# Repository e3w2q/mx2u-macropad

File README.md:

# MX2U!

Happy Holidays Macro Pad.

## What is the MX2U! ?

MX2U! is a macro pad for MX switches that can be used for fun at certain times of the year.

You can place a single 2U key or two 1U keys on this macro pad.

Note: When using the 2U key, the backlight goes directly into your eyes!

## Link

[Hardware data (PCB)](pcb/)

[Firmware](https://github.com/e3w2q/qmk_firmware/tree/e3w2q/keyboards/e3w2q/mx2u)

[PCBの入手方法](doc/pcb_order_guide_jp.md)

[パーツリスト](doc/bom_list_jp.md)

[ビルドガイド](doc/readme_jp.md)

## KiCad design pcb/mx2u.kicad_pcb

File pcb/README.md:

# MX2U! PCB Data

## Schematic
[Schematic PDF](../doc/ukiha.pdf?raw=true)

## PCB Layout

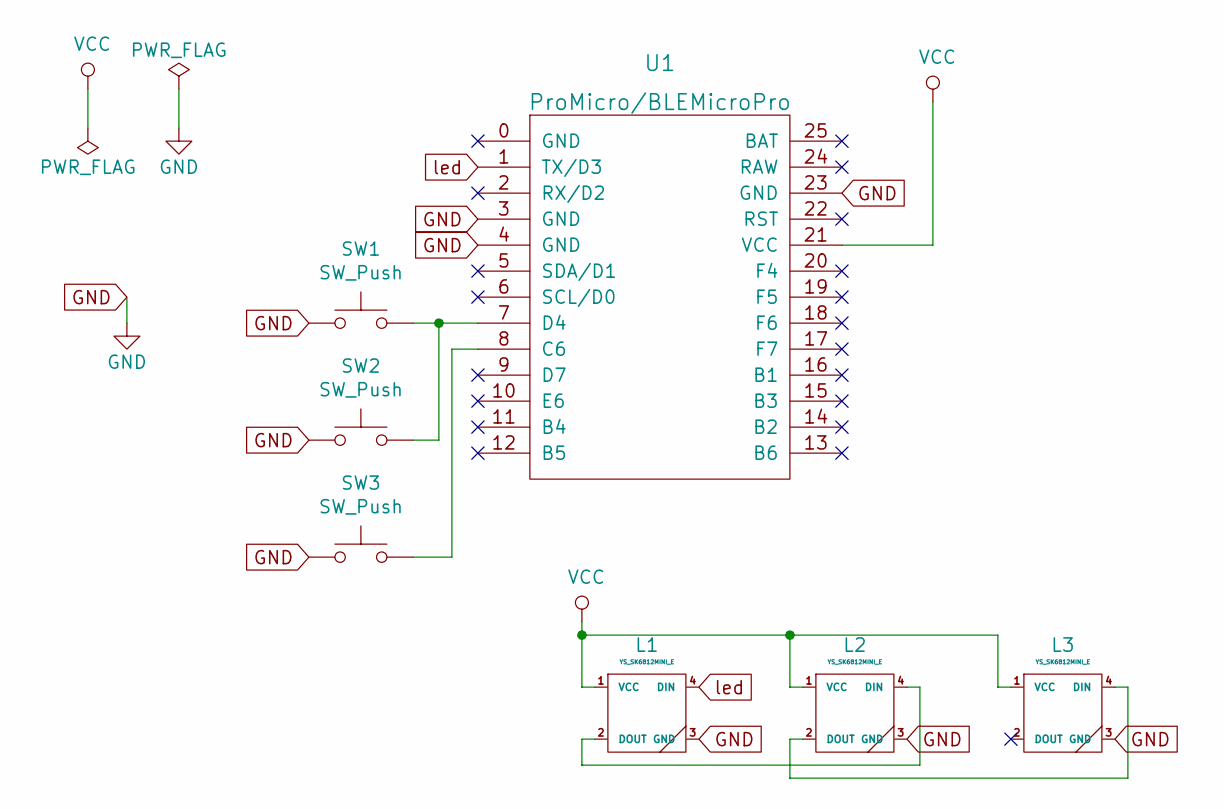
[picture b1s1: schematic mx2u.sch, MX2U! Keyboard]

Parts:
L1, L2: YS_SK6812MINI_E; YS-SK6812MINI-E
L3: YS_SK6812MINI_E; NeoPixcel_Diffused_5mm_Through_Hole_LED
SW1, SW2, SW3: SW_Push; CherryMX_MidHeight
U1: ProMicro/BLEMicroPro; ArduinoProMicro_ConThrough

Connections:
GND: L1.3 (GND), L2.3 (GND), L3.3 (GND), SW1.1, SW2.1, SW3.1, U1.3 (GND), U1.4 (GND), U1.23 (GND)
unnamed: L1.2 (DOUT), L2.4 (DIN)
unnamed: L2.2 (DOUT), L3.4 (DIN)
unnamed: SW1.2, SW2.2, U1.7 (D4)
unnamed: SW3.2, U1.8 (C6)
VCC: L1.1 (VCC), L2.1 (VCC), L3.1 (VCC), U1.21 (VCC)
led: L1.4 (DIN), U1.1 (TX/D3)

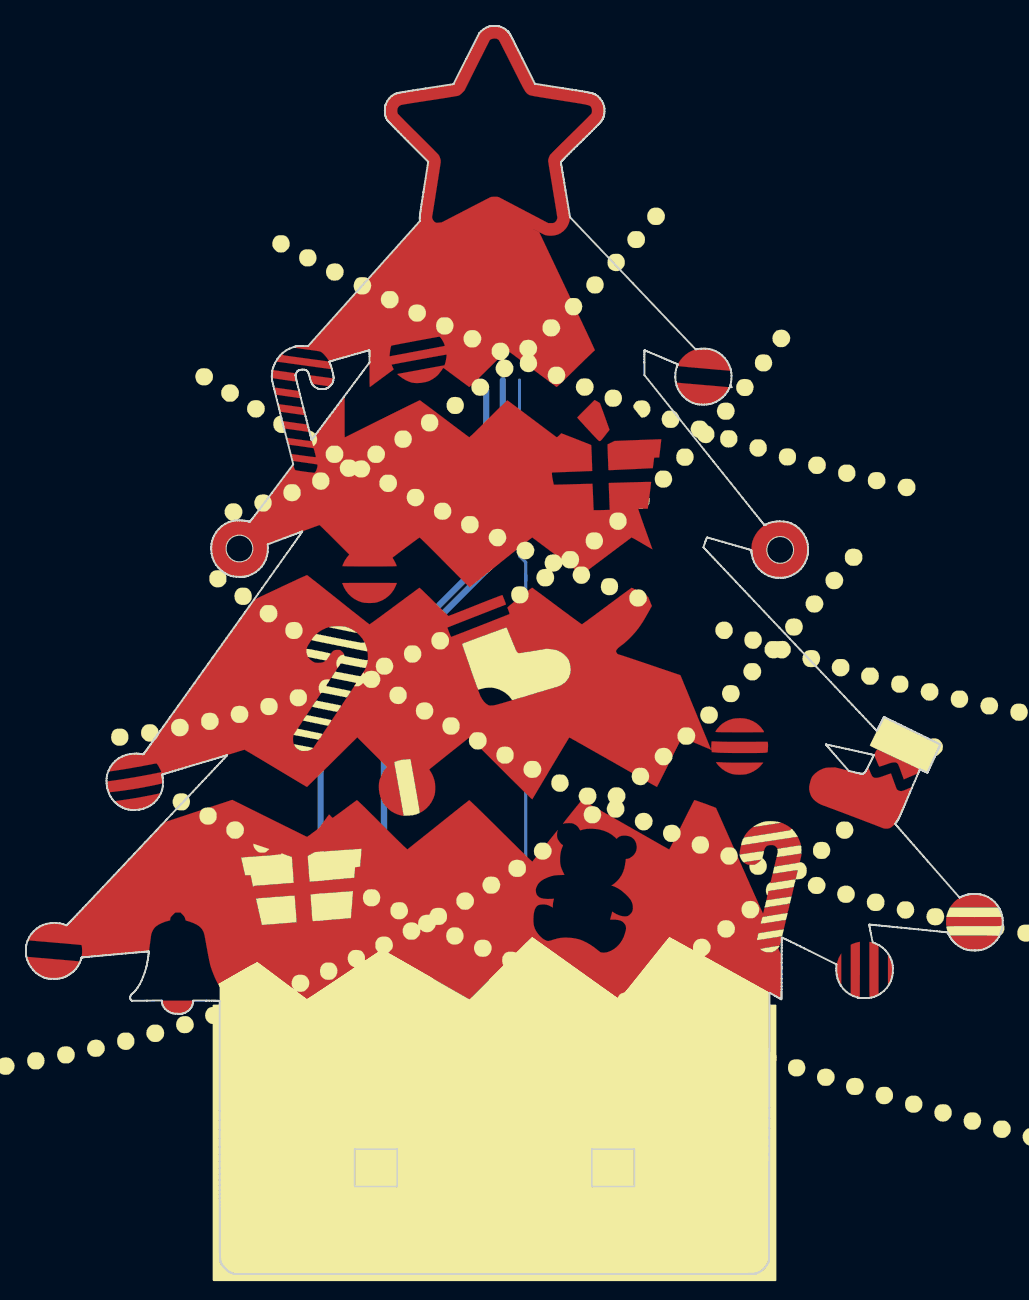
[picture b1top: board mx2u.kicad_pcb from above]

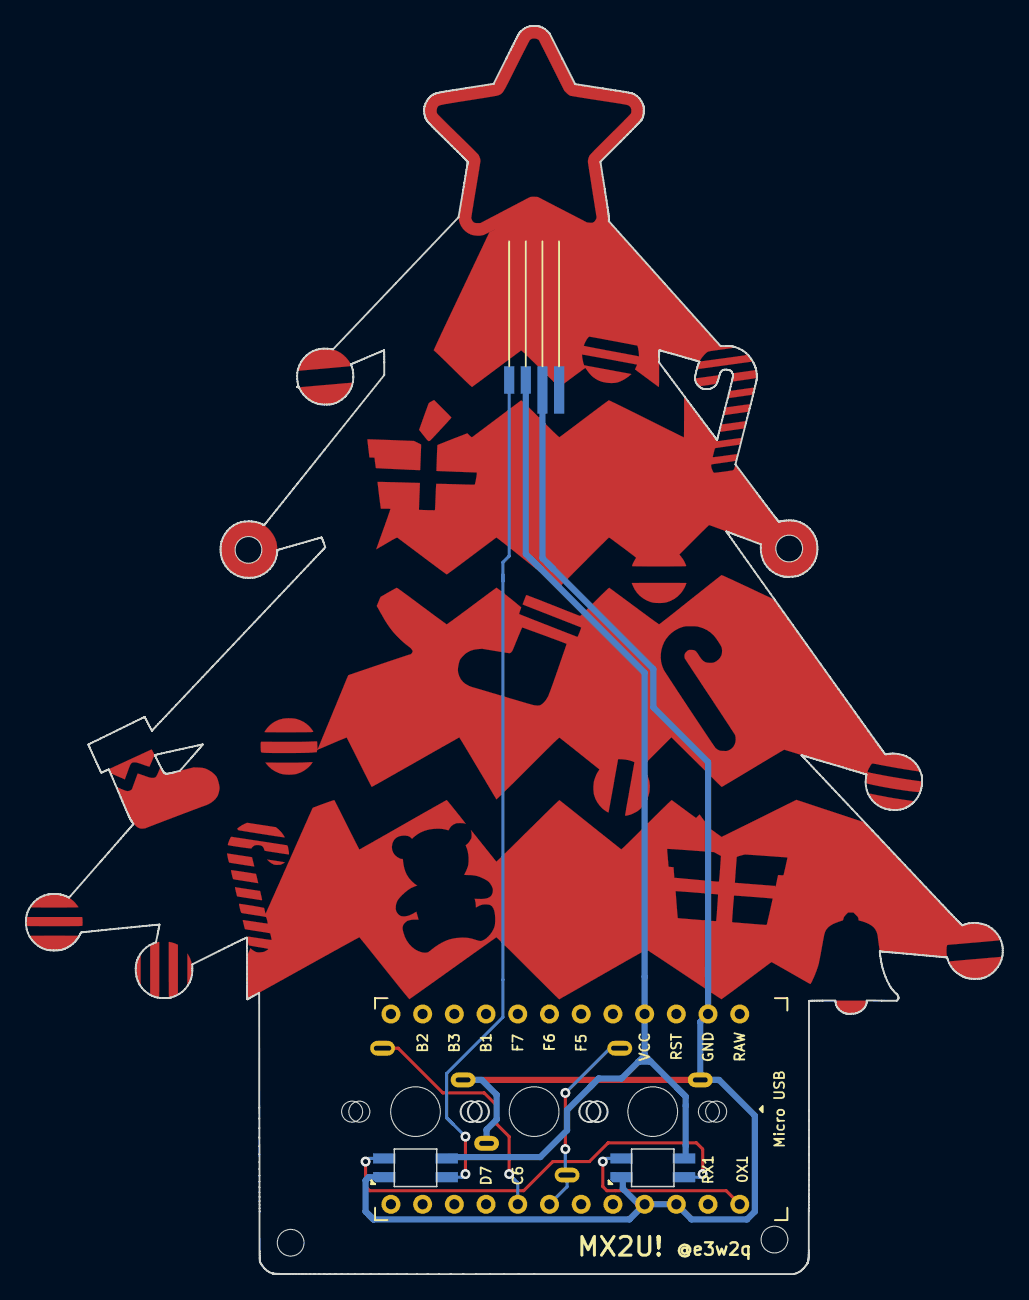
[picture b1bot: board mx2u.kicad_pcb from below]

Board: 2 copper layers, 78.2 x 100.0 mm, 7 parts (2 on the bottom side), 7 nets.

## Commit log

2020-12-05 Add documents

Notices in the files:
README.md:
License: MIT
